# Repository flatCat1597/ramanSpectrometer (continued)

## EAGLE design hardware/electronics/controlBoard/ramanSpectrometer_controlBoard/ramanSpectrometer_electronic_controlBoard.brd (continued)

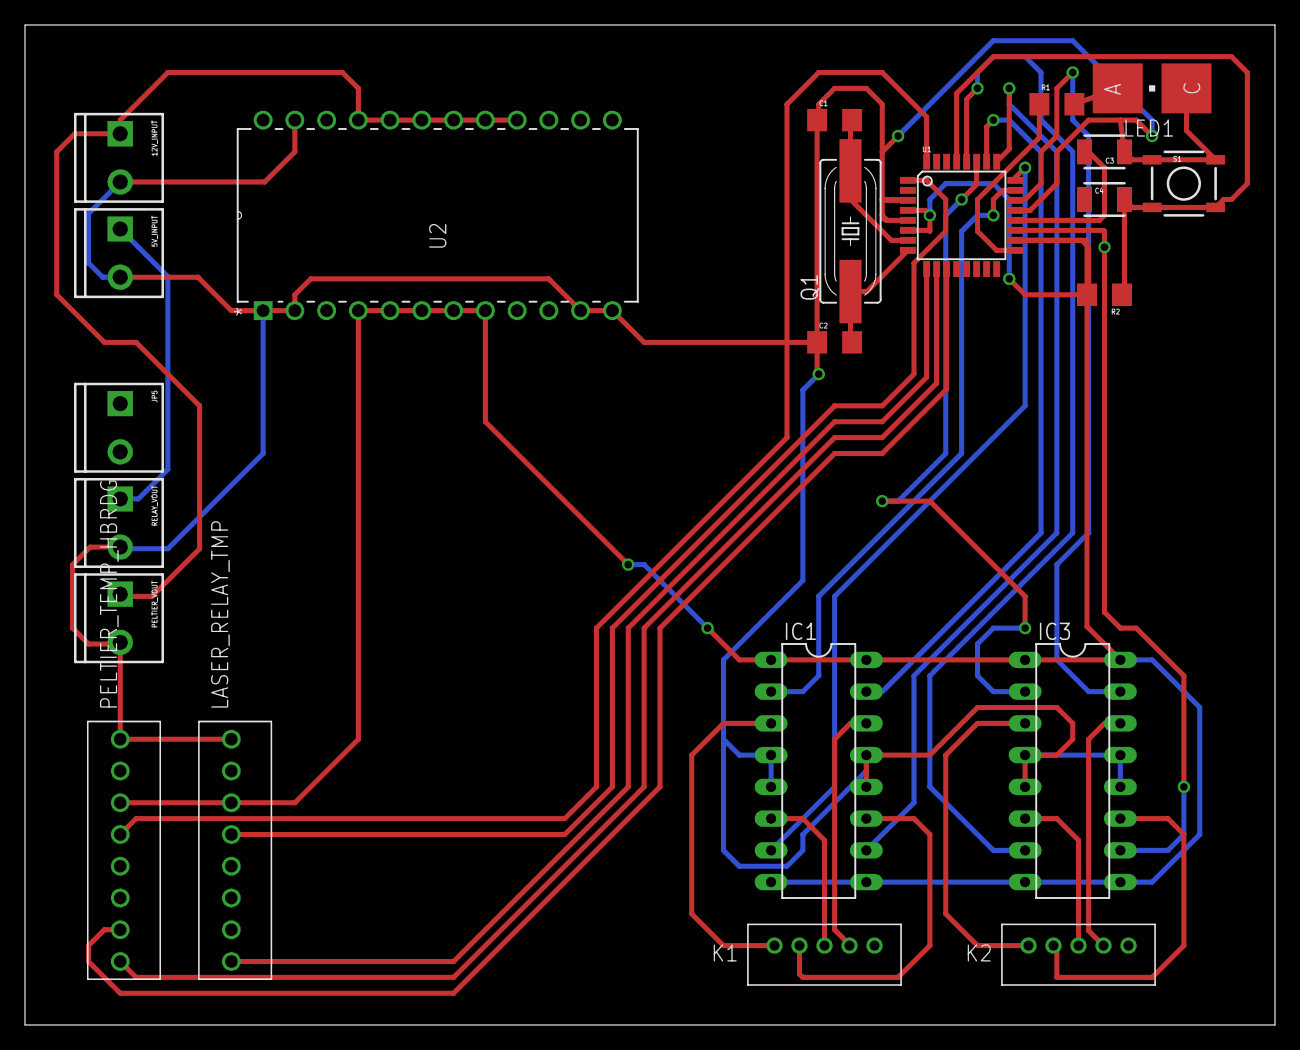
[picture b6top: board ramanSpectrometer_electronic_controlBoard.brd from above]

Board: 2 copper layers, 100.0 x 80.0 mm, 22 parts (0 on the bottom side), 32 nets.

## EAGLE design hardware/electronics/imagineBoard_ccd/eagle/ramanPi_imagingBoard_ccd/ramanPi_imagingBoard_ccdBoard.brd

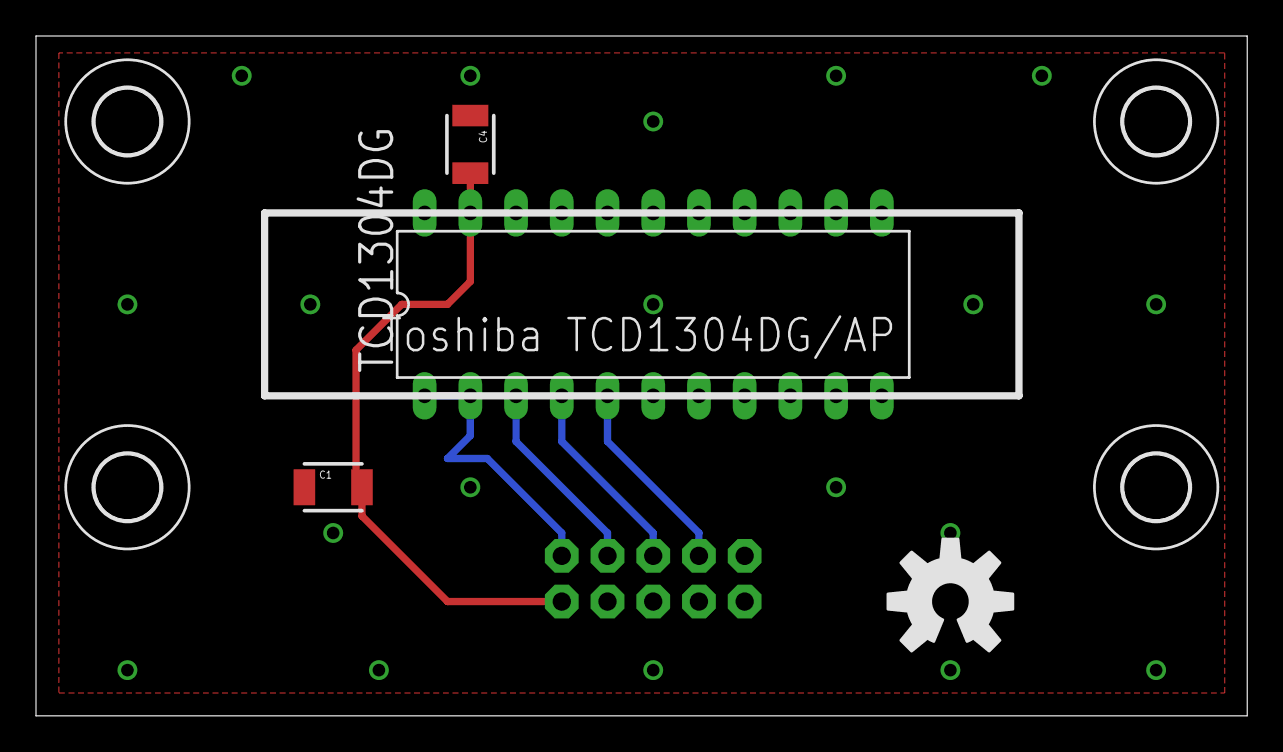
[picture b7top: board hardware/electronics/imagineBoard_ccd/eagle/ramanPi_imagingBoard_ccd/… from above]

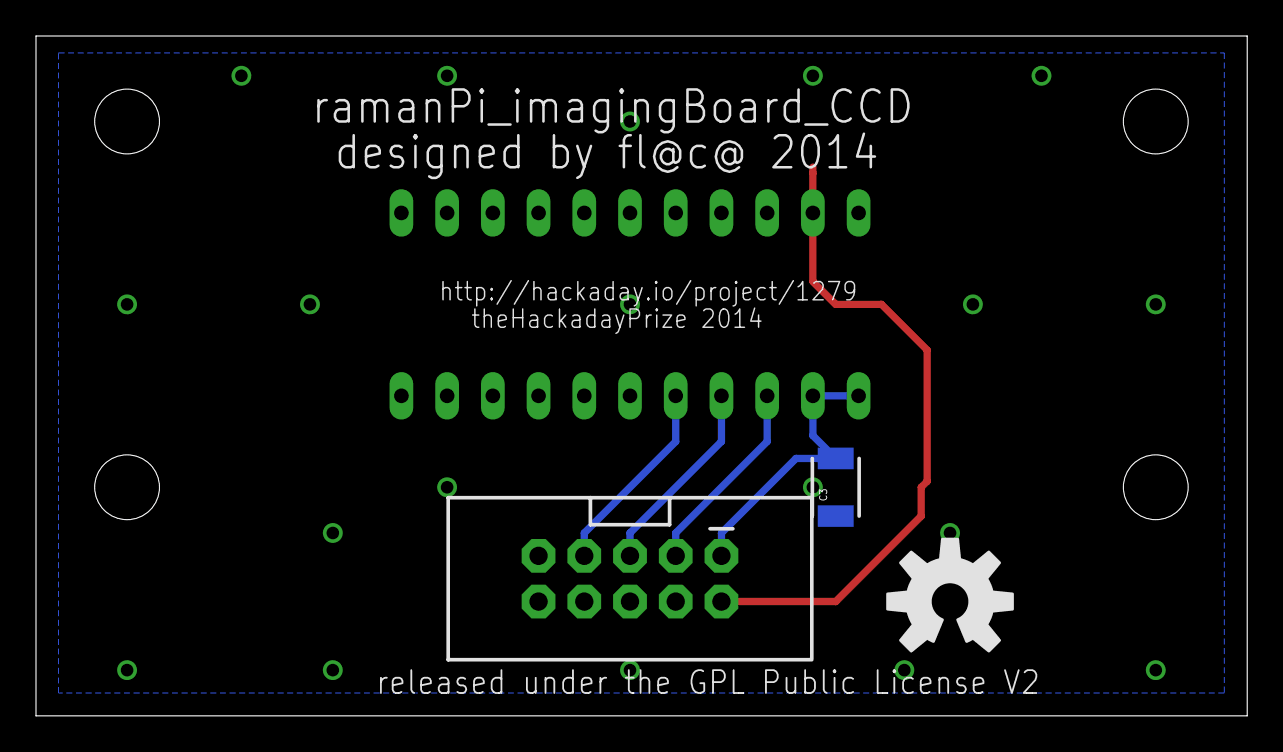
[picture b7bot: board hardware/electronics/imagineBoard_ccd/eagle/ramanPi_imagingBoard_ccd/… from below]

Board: 2 copper layers, 67.3 x 37.8 mm, 11 parts (3 on the bottom side), 6 nets.

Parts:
C1, C3, C4: 0.1uf; 1210
H1, H2, H3, H4: MOUNT-HOLE3.6; 3,6
IMAGINGBOARD: M05X2SHD; 2X5-SHROUDED
TCD1304DG: DIL22-4
U$1, U$2: OSHW-LOGO-L

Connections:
5V: C3.2, IMAGINGBOARD.1, TCD1304DG.1, TCD1304DG.2
GND: C1.1, C3.1, C4.1, IMAGINGBOARD.4, IMAGINGBOARD.6, IMAGINGBOARD.8, IMAGINGBOARD.9, IMAGINGBOARD.10, TCD1304DG.6, TCD1304DG.7, TCD1304DG.8, TCD1304DG.9, TCD1304DG.10, TCD1304DG.11, TCD1304DG.12, TCD1304DG.13, TCD1304DG.14, TCD1304DG.15, TCD1304DG.16, TCD1304DG.17, TCD1304DG.18, TCD1304DG.19, TCD1304DG.20, TCD1304DG.22
unnamed: C1.2, C4.2, IMAGINGBOARD.2, TCD1304DG.21
unnamed: IMAGINGBOARD.5, TCD1304DG.4
unnamed: IMAGINGBOARD.7, TCD1304DG.5
unnamed: IMAGINGBOARD.3, TCD1304DG.3

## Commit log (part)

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2014-05-29 Added Files
    Added all files from original location
2014-05-29 Mirror mount adjustment bracket
    Fixed and updated bracket sizes and recompiled stl files...
2014-05-29 Recompiled .stl files after fixing dimensions
    Mirror micro adjustment bracket needed some size adjustments.. The
    mirror main mount needed updating to the .stl file as well.
2014-05-29 Added keys to objective lens mount for orientation
    Helps orient the top and bottom and lessen likelihood of the mount to
    move, etc..
2014-05-30 Moved into more logical folder arrangements
    Placed all the files into a more logical file arrangement to allow for
    additional categories such as the firmware and other software, etc. to
    be added.
2014-05-30 test software upload for raspi to analyze spectra
    Uploading test software for raspberryPi to image spectra
2014-05-30 update
    nothing special-verbage
2014-05-30 updated the readme file
2014-05-30 Creation and addition of a bunch of images
    images for the website and documentation.
2014-05-30 Updated 532nm Pass Filter Mount
    Needed to update it to fit actual new pass filter
2014-05-30 updated to add index notches
    Added index notches for easier orientation
2014-05-30 Added tray mount for RaspberryPi
    Tray mount includes a thingiverse item I integrated..I'll find the link
    and post it soon...
2014-05-30 Updated 532nmPass Mount
    Modified to adjust the filter thickness..the mirror was a little wobbly
    inside the mount..this should tighten up the tolerances.. Also deleted
    the retired files...
    Other files are from rendering for the project log...
2014-05-30 Included a picture of the ITX Case
    BitFenix Case..photo for the blog..
2014-05-31 Added a few objects to the fullAssembly
2014-05-31 created image for website
    Vertical aperture with collimator lens in place...image created for
    website update.
2014-05-31 A little housecleaning...
    moved some files and directories around, changed some names...
2014-06-01 Added supports to inside of mirror mount.
    While printing the top side of the mount was coming out a little droopy
    on the davinci at least....so I added some supports....Testing them now
    to see if they work....
2014-06-04 testing some display and motor control
    These are mBed online IDE dumps, should be able to import them with no
    problem..
2014-06-05 updated controlBoard tray and the display trim
    Updated the controlBoard tray to accommodate the full pcb, which now
    just slides right into the mount nicely...
    Completely redesigned the display mechanical tray and the faceplace to
    accommodate the new color TFT display and a capacitive backlit touch
    panel that'll be built from scratch..
2014-06-05 rendered some of the faceplate, etc.
    rendered the drive tray and faceplate images for the display so I could
    post an update on the website...
2014-06-06 redesigned the display drive tray and faceplate
    total redesign for the tft display...
2014-06-09 updated new objects
2014-06-10 update name and redesigned objects
    redesigned laser emitter and shutter for better aesthetics and
    functionality
2014-06-10 updated objects
    surfaceMirror module updated
2014-06-10 fixed mirror mount
    errors in printing- resolved
2014-06-11 updates and new images
    Updated the complete system model and rendered some pictures from it for
    the design log..
2014-06-11 created 532nmPassFilterMount
    Need to fix errors for printing...
2014-06-16 beginning design for controlBoard
    updated design overview image and began design for controlBoard
2014-06-19 updated controlBoard schematics
2014-06-20 Renderings for website
2014-06-24 further design for objectiveLensMount
2014-06-25 revising some file names and paths
    moved some files to the new path, renamed some libraries and other
    files..
2014-07-02 syncUp
2014-07-02 updated controlBoard schematic and board
2014-07-11 rendered some pix for the video
2014-07-17 protocol ctrlBd-raspi tests
    testing protocol between raspi and controlBoard
2014-07-23 fixing errors in objective lens mount
2014-07-23 fixed minor errors and new tests
    minor errors in mirror mount
    uploaded new firmware tests and python code
2014-07-29 fixed objectiveLensMount
    Made the upper and lower pieces more printable by ordering the unions,
    etc. properly...
2014-07-29 more work on the filter selection wheel
    added:
    filter holes
    bearing holes
    central hub
    moved center of wheel
2014-07-30 working on filter wheel assembly
    Added bearing mounts and a number of other details...
2014-08-01 Added screw paths to mirror mount, added/modified web pix
    Added screw paths to mirror mount to allow for clearance of screws when
    assembling... Need to add adjustment screws and grommet groove as well.
2014-08-02 Fixed Filter Wheel Assembly
    Fixed some errors that were preventing it from printing properly..
    The main body now prints..
2014-08-08 Added openSource License Info and keypadTemplate
2014-08-08 more licensing fun
    Added pages from spreadsheet for web....
2014-08-11 Fixed display and keypad mount
    Angled it at a 45deg angle for mounting to the front of the case..
    Added some pics for ccd testing..
2014-08-13 updates to spectrometer design
    working on outer casing
2014-08-14 added test stands for optics
    added test stands for spectrometer optics..
    will be used to determine focal lengths and angles
2014-08-15 updateTestStands and updated firmware source
    Updated optics_module_testStand_***** for testing optics
    Updated source code for the controlBoard, interfaceBoard and
    imagingBoard
    They now contain all combinations of exports from the online compiler
2014-08-16 fixed optics_module_testStand_lightMount
    Added lens mount for collimating lens testing
2014-08-17 Re-write imagingBoard firmware
    more intelligent synchronization For clock signals
2014-08-18 testing
    testing
2014-08-19 updated python and firmware for imagingBoard
    Added python code for raspi to retrieve image data from imagingBoard...
    Updated firmware for imagingBoard to capture CCD data into an array then
    dump to serial when finished.
2014-08-21 refresh for openSource library information
    re-uploaded xls and pdf for openSource hardware and library info...
2014-08-26 designRefresh for Spectrometer module
    Completely redesigning the geometry... when you change the angle of a
    mirror, or grating, the rest of the positions for other objects are
    automatically calculated
2014-08-28 added flat mirror reflectance test
    test module to calculate angle of reflection on a flat mirror.
    works. each module needs to be modified to take variables
2014-08-28 added curved mirror reflectance test
    test module to calculate reflection angle on a curved mirror
    works. need to add compensation for mirror rotation
    currently only works in two dimensions, need to add 3rd
2014-08-30 major work done to spectrometer
    Spectrometer near complete.
    too many new things to list...
2014-09-02 Major updates to spectrometer
    Adding mounts for optics and adjusting case size and shape..
2014-09-08 breakoutComponentsForPrintAndAddTopCover
    Break out all components of spectrometer for printing..
    Created top cover for spectrometer
2014-09-09 fixed top cover and added light baffles
    Fixed inside cylinder for top cover to make it fit into hole..
    Added light baffles for inside spectrometer.
2014-09-11 minorUpdate to spectrometer
    Included some needed attributes
    adjusted working resolution lower for faster rendering
2014-09-13 created laserTestStand with vial and filter holder
    test stand for 532nm laser
    holds vial and filter
2014-09-13 experimenting
    experimenting
2014-09-16 updated imagingBoard schematic
    Added DS18B20 to schematic
2014-09-17 Updated Spectrometer
    made the access cover screw holes slightly larger
    made inside base for diffraction grating mount slightly larger
    also made outer diameter of diffraction grating mount slightly larger
2014-09-17 fixed laser test stand - dgmount
    Made flange mount more substantial
    corrected size for DG Mount base
2014-09-18 updated imagingBoard firmware and pc software
    Added serial control for sensitivity
2014-09-19 updated beam splitter assembly
    Added access port cover
    Added beam splitter mount
    Fixed center hub and cross beam path
2014-09-19 updated splitter and filter
    made splitter mount thicker
    made more room for 550nm filter
    modified hub to allow for clearance
2014-09-20 edited filter selector center hub
    modified center hub to fit flush
2014-09-20 minor adjustments to filter selector assembly
    minor clearance issues fixed
2014-09-21 update laser shutter
    new flange faces for laser shutter assembly
    screw mounts for servo
    close rear window to block incident light
2014-09-21 updated laser mount
    Updated laser mount to integrate 532nm pass filter into the laser
    mount.. This allows for some space saving to fit into the system case..
2014-09-22 updated objective lens mount
    fixed dimensions for object lens to better fit
    adjusted mounting screw holes to allow for shorter screws
    removed slits on sides to better block ambient and incidental light -
    also stronger structurally
2014-09-22 updated surface mirror mount
    added adjustment screwpoints..
    updated screw holes for better positioning
2014-09-22 updated spectrometer
    reoriented flange face - rotated 90deg to allow for vertical mounting
    and have full face contact
2014-09-23 updated surface mirror mount
    Adjusted screw holes to fit M2 Socket Cap Screws
2014-09-26 controlBoard schematics
    updating controlBoard schematics and eagle files
2014-09-29 new schematics
    powerControlBoard and interfaceBoard schematics
2014-10-06 controlBoard new schematic and board layout
    New board layout and schematic for controlBoard
2014-10-07 re-routed controlBoard layout
    controlBoard board layout redone..
    Adjusted stepper controller placement
    Adjusted board size
    Added svg exports for top and bottom layers
    Added top and bottom studio files for cameo
2014-10-08 interfaceBoard schematic and board layout
    created interfaceBoard schematic and board layout eagle files
    also included .studio files for cameo as well as images
2014-10-08 imagingBoard schematic and board layout
    created new imaging board layout
    added color sensor and uv index sensor
    added status, busy and test led
    added ccd temperature sensor
2014-10-08 fixed silkscreen for imagingBoard
    ccdTemp label said laserTemp - fixed, now says ccdTemp
2014-10-09 imagingBoard_ccd schematic and board layout
    created imagingBoard_ccd
2014-10-09 imagingBoard updated
    updated pin configuration for remote ccd board to match with new pinout
    added ground plane and decoupling caps
2014-10-09 updated Nucleo library in all board layouts
    Updated Nucleo F401_RE library for better drill hole sizes
    updated all boards to include new library changes
    ---need to update all studio files, svg, etc..
2014-10-10 powerControlBoard schematic and board layout
    created schematic and board layout for powerControlBoard
2014-10-15 added reset circuitry to all stm32 boards
    added reset circuitry for raspi to reset each board from remote.
2014-10-16 new spectral imaging software
    now called spectraCide
    shares data online through plot.ly
    will be adding a gui very soon
2014-10-17 spectraCide v0.1
    QT GUI for spectraCide
    sends data to plotly
    saves png of plot
2014-10-17 spectraCide tests
2014-10-23 new imagingBoard firmware
    too many changes to list
    RTOS, timing, no PWM, and so on..
2014-10-24 new cuvette tray assembly
    fixed some minor details and added a thicker door
2014-10-24 keeping a history
    back versions of XYZware and firmware in case they decide to "update"
    again...
2014-10-27 tweaks
    minor updates to a couple things
    added safety mount for laser relay board
    updated bill of materials
    adjusted cuvette tray dimensions
2014-11-04 --
    --
2015-03-20 ..
    ..
